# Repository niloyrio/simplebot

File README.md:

# SimpleBot

Bespoke Robot Society's original design for kids, students, or cost-sensitive tinkerers.

Goals:

* Control a basic, multipurpose teaching robot with the Pi Pico (or Pico W).
* Demonstrate **optical odometry** - measuring the distance wheels turn by counting pulses on light sensors.
* Demonstrate **line following** - steer the robot in response to reflectance sensors that give the position of the line.
* Leave pins open on the microcontroller for additional upgrades.
* **Do not exceed $20 in price, with batteries included.**

## Hardware

Simplebot is based on the "Arduino Smart Car" kit that can be found on Amazon or Aliexpress. This provides a caster wheel, two yellow "TT" motors with optical encoder wheels and actual wheels, a power switch, and a 4xAA battery case. (~$6)

For line detectors, a generic "Infrared Obstacle Avoidance Sensor" module can be found in the US for 20 for $10 - SimpleBot requires two ($1).

Microcontroller - Raspberry Pi Pico ($4) or Raspberry Pi Pico W ($6).

Motor Controller - The TB6612FNG dual H-bridge module. You might be able to find this for $1 or less from overseas, but 3 for $9 is available in the US. ($3)

The optical encoder module requires one LED, one photoresistor, five resistors, and one LM393 chip for both. I don't know the prices for these, as I had them on hand.

an MPU6050 (Accelerometer/gyroscope) and nRF24l01 (2.4GHz radio module) are included on the circuit board, but haven't been tested or programmed yet. These occupy the I2C and SPI buses respectively, and would play well with some additional sensors (at the cost of spare pins for more SPI devices).

## Circuit Board

The protoboard design included uses all through-hole components.

PCB design is still to-do.

The current protoboard pinout leaves 7 GPIOs open on the Pi Pico, including UART 0 and all three ADCs. 

## Software

Copy the included files to your Pi Pico by USB cable. I used Thonny to test the robot's programs.

# Future Work

Should I switch to an off-the-shelf optical encoder module, or should I build a custom line detecting sensor?

Printed circuit boards:

* Through hole soldering kit
* a board-on-board PCB - same layout as the protoboard, but soldered flat together.
* a custom PCB that uses the ICs from the modules directly

SimpleBot is unfortunately too large for standard micromouse mazes, so a "simplebot mini" seems to be in order.

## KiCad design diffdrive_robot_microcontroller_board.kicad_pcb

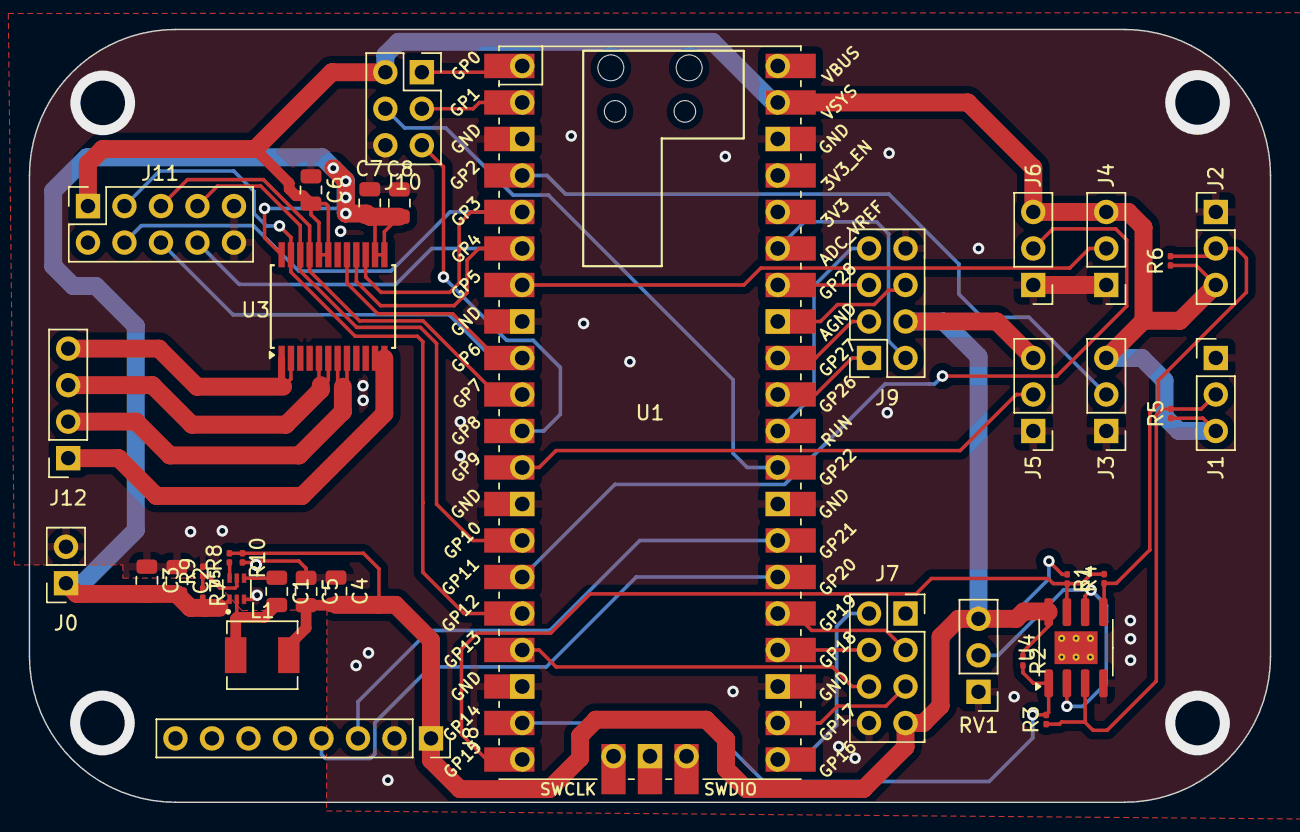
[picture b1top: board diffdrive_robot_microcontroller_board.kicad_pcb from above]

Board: 2 copper layers, 86.4 x 53.8 mm, 37 parts (0 on the bottom side), 43 nets.

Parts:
C1, C2, C4, C6, C7: 100nF; C_0805_2012Metric
C3, C5, C8: 22uF; C_0805_2012Metric
J0: Battery_Input; PinSocket_1x02_P2.54mm_Vertical
J1: Odom L; PinHeader_1x03_P2.54mm_Vertical
J2: Odom R; PinHeader_1x03_P2.54mm_Vertical
J3: Sensor A; PinHeader_1x03_P2.54mm_Vertical
J4: Sensor B; PinHeader_1x03_P2.54mm_Vertical
J5: Sensor C; PinHeader_1x03_P2.54mm_Vertical
J6: Sensor D; PinHeader_1x03_P2.54mm_Vertical
J7: nRF24L01 Connector; PinSocket_2x04_P2.54mm_Vertical
J8: i2c accel/gyro; PinSocket_1x08_P2.54mm_Vertical
J9: analog_expansion; PinSocket_2x04_P2.54mm_Vertical
J10: digital_expansion; PinSocket_2x03_P2.54mm_Vertical
J11: external_hbridge; PinSocket_2x05_P2.54mm_Vertical
J12: Motor_Pins; PinSocket_1x04_P2.54mm_Vertical
L1: 2.2uH; L_Sunlord_MWSA0402S
R1, R2: 1k; R_0201_0603Metric
R3, R4: R_hysteresis; R_0201_0603Metric
R5, R6, R7: 100K; R_0201_0603Metric
R8: 30.9K; R_0201_0603Metric
R9: 15.4K; R_0201_0603Metric
R10: 10K; R_0201_0603Metric
RV1: R_Potentiometer; PinHeader_1x03_P2.54mm_Vertical
U1: Pico; RPi_Pico_SMD_TH
U3: TB6612FNG; SSOP-24_5.3x8.2mm_P0.65mm
U4: LM393; SOIC-8-1EP_3.9x4.9mm_P1.27mm_EP2.29x3mm_ThermalVias
U5: TPS562242DRLR; SOT50P160X60-6N

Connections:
+3V3: C4.2, C5.2, C6.2, J1.3, J2.3, J3.3, J4.3, J5.3, J6.3, J7.7, J8.1, J9.4, J10.2, J11.1, J11.2, L1.2, R1.1, R2.1, R5.1, R6.1, R8.2, R10.1, RV1.3, U1.39 (VSYS), U3.19 (STBY), U3.20 (VCC), U4.8 (V+)
+BATT: C2.2, C3.2, C7.2, C8.2, J0.1, R7.2, U3.13 (VM2), U3.14 (VM3), U3.24 (VM1), U5.1 (VIN)
ADC0: J9.1, U1.31 (GPIO26_ADC0)
ADC1: J9.3, U1.32 (GPIO27_ADC1)
ADC2: J9.5, U1.34 (GPIO28_ADC2)
AGND: J9.6, U1.33 (AGND)
AIN1: J11.5, U1.10 (GPIO7), U3.21 (AIN1)
AIN2: J11.7, U1.14 (GPIO10), U3.22 (AIN2)
AVREF: J9.2, U1.35 (ADC_VREF)
BIN1: J11.6, U1.9 (GPIO6), U3.17 (BIN1)
BIN2: J11.8, U1.6 (GPIO4), U3.16 (BIN2)
CE: J7.6, U1.17 (GPIO13)
CSN: J7.5, U1.22 (GPIO17)
GND: C2.1, C3.1, C4.1, C5.1, C6.1, C7.1, C8.1, J0.2, J1.1, J2.1, J3.1, J4.1, J5.1, J6.1, J7.8, J8.2, J9.8, J10.6, J11.9, J11.10, R9.2, R10.2, RV1.1, U1.3 (GND), U1.8 (GND), U1.13 (GND), U1.18 (GND), U1.23 (GND), U1.28 (GND), U1.38 (GND), U3.3 (PGND1), U3.4 (PGND1), U3.9 (PGND2), U3.10 (PGND2), U3.18 (GND), U4.4 (V-), U5.3 (GND)
GP0: J10.1, U1.1 (GPIO0)
GP1: J10.3, U1.2 (GPIO1)
GP8: J10.5, U1.11 (GPIO8)
GP22: J10.4, U1.29 (GPIO22)
MISO: J7.2, U1.21 (GPIO16)
MOSI: J7.3, U1.25 (GPIO19)
unnamed: J1.2, R3.1, R5.2, U4.3 (+)
unnamed: J2.2, R4.1, R6.2, U4.5 (+)
unnamed: J3.2, U1.4 (GPIO2)
unnamed: J4.2, U1.7 (GPIO5)
unnamed: J5.2, U1.12 (GPIO9)
unnamed: J6.2, U1.15 (GPIO11)
unnamed: J12.1, U3.11 (BO1), U3.12 (BO1)
unnamed: J12.2, U3.7 (BO2), U3.8 (BO2)
unnamed: J12.3, U3.5 (AO2), U3.6 (AO2)
unnamed: J12.4, U3.1 (AO1), U3.2 (AO1)
unnamed: R2.2, R3.2, U1.19 (GPIO14), U4.1
unnamed: R1.2, R4.2, U1.20 (GPIO15), U4.7
unnamed: RV1.2, U4.2 (-), U4.6 (-)
unnamed: C1.1, U5.4 (BST)
unnamed: R7.1, R9.1, U5.5 (EN)
unnamed: R8.1, U5.6 (FB)
PWMA: J11.3, U1.16 (GPIO12), U3.23 (PWMA)
PWMB: J11.4, U1.5 (GPIO3), U3.15 (PWMB)
RUN: J9.7, U1.30 (RUN)
SCK: J7.4, U1.24 (GPIO18)
SCL: J8.3, U1.27 (GPIO21)
SDA: J8.4, U1.26 (GPIO20)
SW: C1.2, L1.1, U5.2 (SW)

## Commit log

2024-09-26 initial release
2024-09-26 Add Picture
2024-09-26 Wiring Diagram
2024-09-26 Add wiring diagram to README
2024-12-26 [ImgBot] Optimize images
    *Total -- 614.10kb -> 483.70kb (21.23%)
    /images/Protoboard Wiring Overview.png -- 316.49kb -> 196.80kb (37.82%)
    /images/simplebot.jpeg -- 297.61kb -> 286.90kb (3.6%)
2024-12-26 Add files via upload
    SMD Version of the PCB
